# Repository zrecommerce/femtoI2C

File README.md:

femtoI2C
========

A neat way to add extra GPIO pins to any micro controller using TWI/I2C

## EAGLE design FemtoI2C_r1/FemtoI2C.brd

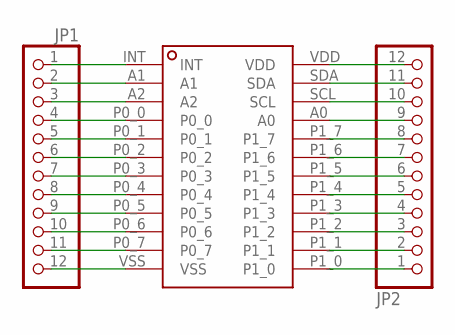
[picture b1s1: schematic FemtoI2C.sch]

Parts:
JP1, JP2: PINHD-1X12; 1X12
U$1: PCA9555A_TSSOP24

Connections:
unnamed: JP1.1, U$1.INT
unnamed: JP1.2, U$1.A1
unnamed: JP1.3, U$1.A2
unnamed: JP1.4, U$1.P0_0
unnamed: JP1.5, U$1.P0_1
unnamed: JP1.6, U$1.P0_2
unnamed: JP1.7, U$1.P0_3
unnamed: JP1.8, U$1.P0_4
unnamed: JP1.9, U$1.P0_5
unnamed: JP1.10, U$1.P0_6
unnamed: JP1.11, U$1.P0_7
unnamed: JP1.12, U$1.VSS
unnamed: JP2.1, U$1.P1_0
unnamed: JP2.2, U$1.P1_1
unnamed: JP2.3, U$1.P1_2
unnamed: JP2.4, U$1.P1_3
unnamed: JP2.5, U$1.P1_4
unnamed: JP2.6, U$1.P1_5
unnamed: JP2.7, U$1.P1_6
unnamed: JP2.8, U$1.P1_7
unnamed: JP2.9, U$1.A0
unnamed: JP2.10, U$1.SCL
unnamed: JP2.11, U$1.SDA
unnamed: JP2.12, U$1.VDD

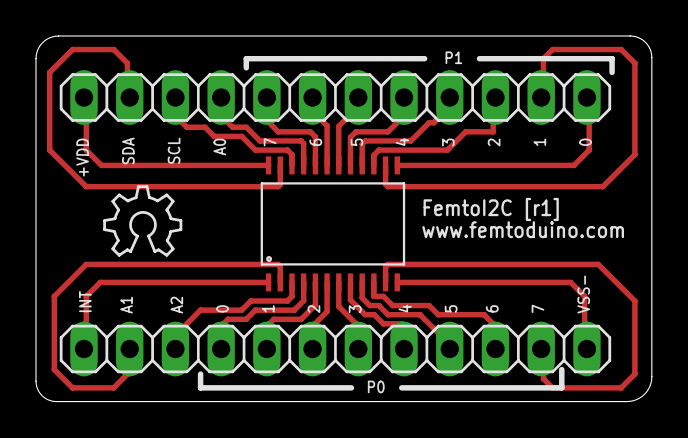
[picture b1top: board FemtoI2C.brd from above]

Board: 2 copper layers, 34.2 x 20.3 mm, 4 parts (0 on the bottom side), 24 nets.

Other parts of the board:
U$2: OSHW_6X150_NOTEXT

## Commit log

2013-07-18 Adding the EAGLE PCB design files.
2013-08-07 Adding in sample sketch
2013-08-28 Adding PDF, and pinout diagram, with pin addresses
2013-08-28 Updating the sample sketch
